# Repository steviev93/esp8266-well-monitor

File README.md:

ESP8266 Well Water Monitor

A solar-powered IoT system for remotely monitoring residential well-water depth using an ESP8266, ADS1115 ADC, and 4–20 mA submersible pressure sensor.

Overview

The monitor converts the sensor's 4–20 mA output into a measurable voltage using a 150 Ω shunt resistor, producing approximately 0.6–3.0 V across the sensor's operating range. An ADS1115 digitizes the signal and communicates with the ESP8266 over I²C.

The ESP8266 processes the reading, converts it into water-level data, and transmits telemetry over Wi-Fi. The sensor loop is switched by a MOSFET so it can be powered only when a measurement is required.

Hardware
ESP8266 NodeMCU
ADS1115 16-bit ADC
4–20 mA submersible pressure/depth sensor
150 Ω current-shunt resistor
IRLB8721 MOSFET for sensor power control
12 V LiFePO4 battery
Solar charging system
Custom KiCad PCB

KiCad schematic and PCB source files are available in hardware/.

Firmware

Firmware is written in C and organized into separate hardware, driver, service, and application layers.

Key features include:

ADS1115 I²C driver
4–20 mA signal conversion and water-level calculation
Wi-Fi connection management
HTTP telemetry
In-memory buffering during connection failures
NVS-backed storage for retained data/configuration
Automatic replay of buffered telemetry after reconnect
Health monitoring and recovery logic
PCB V1 Erratum

The first PCB revision contained an error in the ADS1115 power connection. The ADC supply was routed to the wrong ESP8266 board power connection rather than the regulated 3.3 V rail, resulting in unstable operation and ESP8266 resets.

The prototype was reworked by cutting the incorrect VCC trace and manually connecting the ADS1115 supply to 3.3 V.

A future PCB revision should correct the power-net assignment in the schematic/layout.

Repository Structure
application/ – sampling, telemetry, buffering, supervision
drivers/ – ADS1115 device driver
hal/ – GPIO and I²C hardware abstraction
services/ – Wi-Fi, HTTP, and persistent storage
hardware/ – KiCad schematic, PCB layout, and schematic image
main/ – application entry point
Status

Functional prototype and firmware complete. Hardware design is retained in the repository for continued PCB revision and field-development work.

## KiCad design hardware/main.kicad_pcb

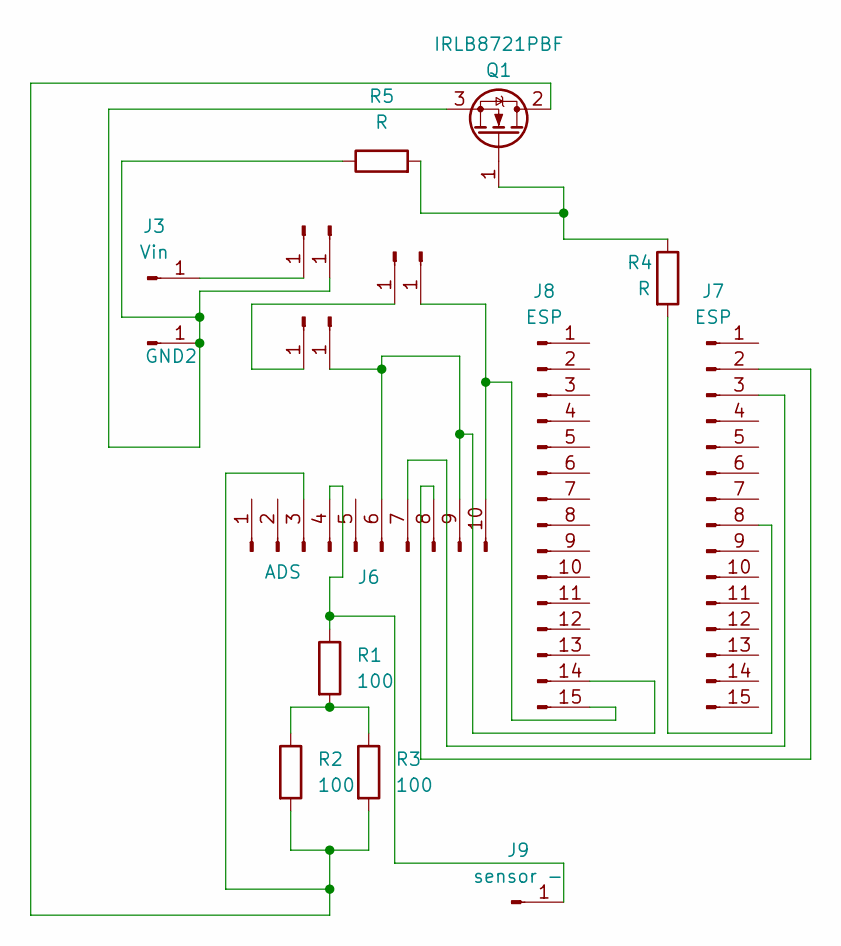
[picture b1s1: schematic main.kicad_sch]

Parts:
GND2: GND2; PinHeader_1x01_P2.54mm_Vertical
J1: BI+; PinHeader_1x01_P2.54mm_Vertical
J2: BI-; PinHeader_1x01_P2.54mm_Vertical
J3: Vin; PinHeader_1x01_P2.54mm_Vertical
J4: BO+; PinHeader_1x01_P2.54mm_Vertical
J5: BO-; PinHeader_1x01_P2.54mm_Vertical
J6: ADS; PinHeader_1x10_P2.54mm_Vertical
J7, J8: ESP; PinHeader_1x15_P2.54mm_Vertical
J9: sensor -; PinHeader_1x01_P2.54mm_Vertical
J10: F+; PinHeader_1x01_P2.54mm_Vertical
J11: F-; PinHeader_1x01_P2.54mm_Vertical
Q1: IRLB8721PBF; TO-220-3_Vertical
R1, R2, R3: 100; R_Axial_DIN0204_L3.6mm_D1.6mm_P7.62mm_Horizontal
R4, R5: R; R_Axial_DIN0204_L3.6mm_D1.6mm_P7.62mm_Horizontal

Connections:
unnamed: GND2.1, J2.1, Q1.3 (S), R5.1
unnamed: J1.1, J3.1
unnamed: J5.1, J6.6, J6.9, J8.14
unnamed: J6.3, Q1.2 (D), R2.2, R3.2
unnamed: J6.4, J9.1, R1.1
unnamed: J6.7, J7.3
unnamed: J6.8, J7.2
unnamed: J7.8, R4.2
unnamed: J4.1, J10.1
unnamed: J6.10, J8.15, J11.1
unnamed: Q1.1 (G), R4.1, R5.2
unnamed: R1.2, R2.1, R3.1

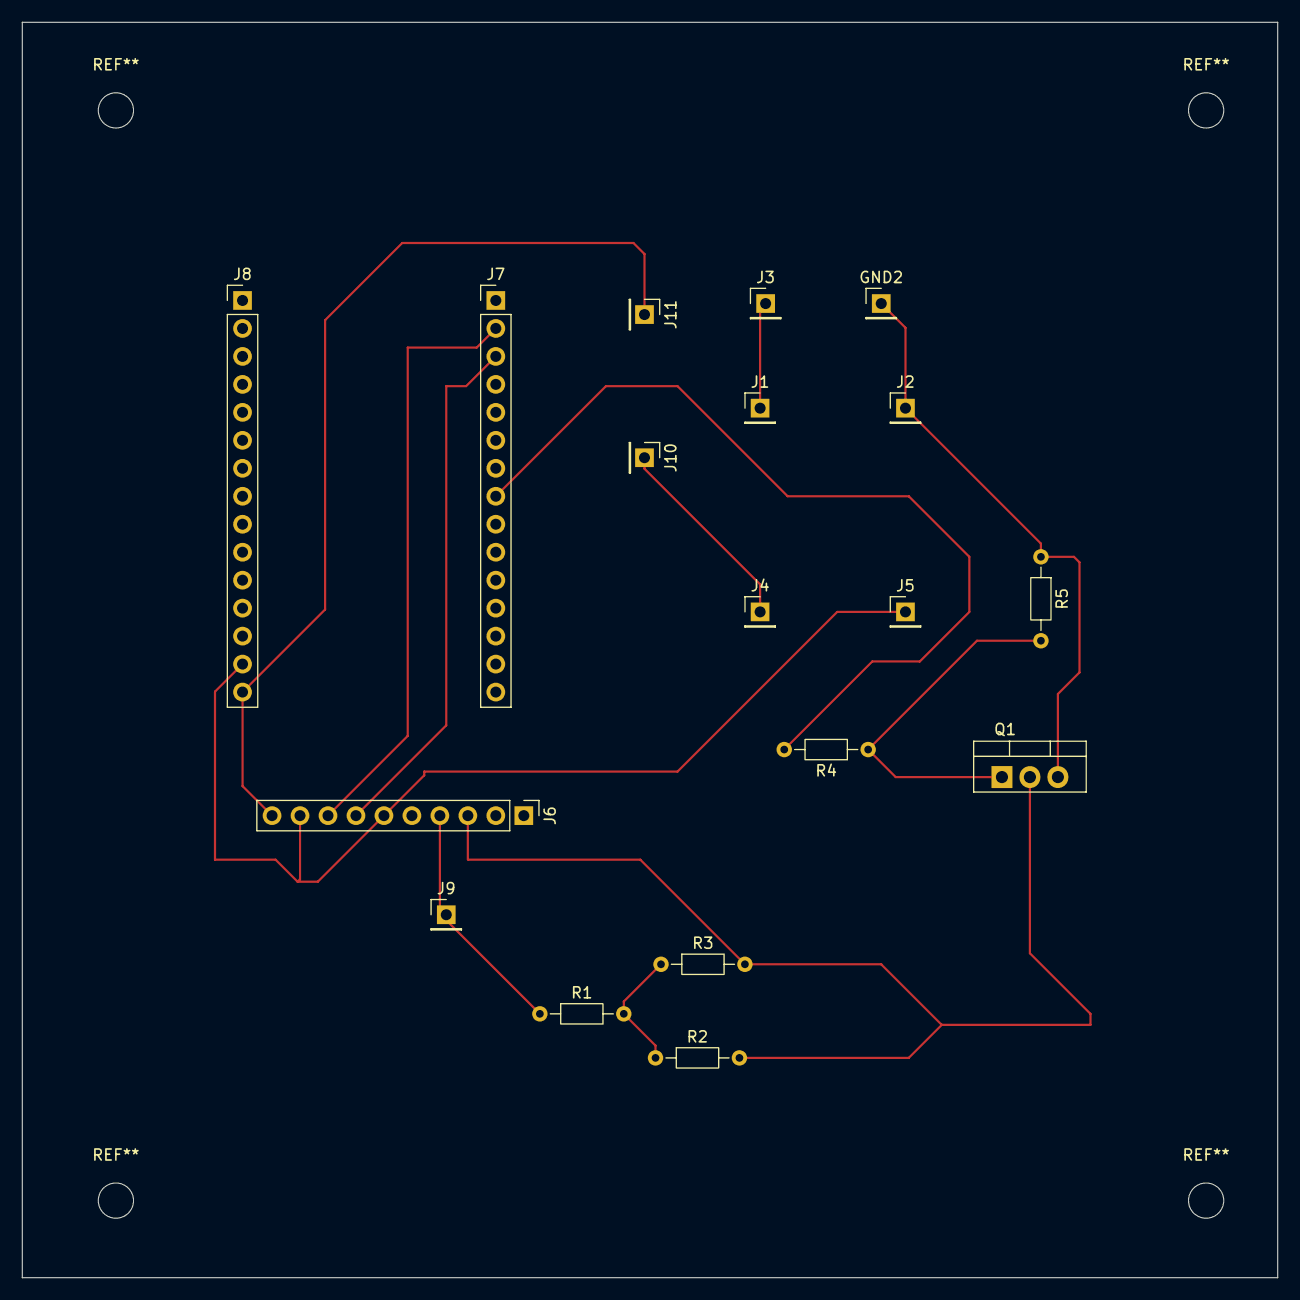
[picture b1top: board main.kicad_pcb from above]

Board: 2 copper layers, 114.0 x 114.0 mm, 18 parts (0 on the bottom side), 12 nets.
